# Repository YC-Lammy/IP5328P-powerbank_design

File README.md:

# IP5328P-powerbank_design
 a PD powerbank pcb based on IP5328P chip, feel free to use it
 
 - support QC2.0/QC3.0 output
 - Support FCP input/output
 - Support AFC input/output
 - Support SFCP input/output
 - Support MTK PE1.1&2.0 output
 - Support USB C DRP input/output
 - Support BC1.2, Apple, Samsung
 - Support PD2.0 bi-directional input/output protocol
 - Support PD3.0 input/output and PPS output protocol
 - Support 5V@3.1A, 9V@2.0A, 12V@1.5A voltage output
 
  Kicad nightly 5.99

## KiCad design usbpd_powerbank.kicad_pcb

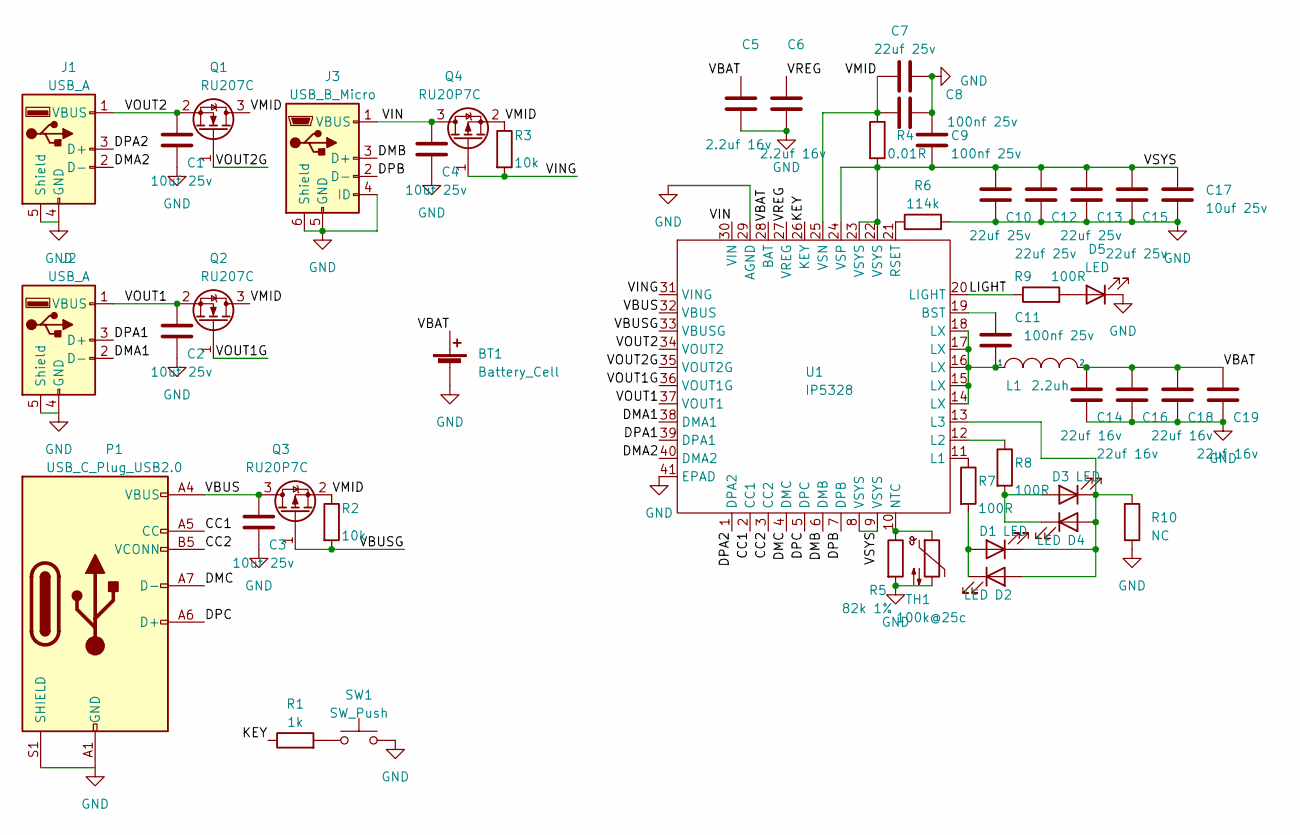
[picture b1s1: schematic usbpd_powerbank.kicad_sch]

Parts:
BT1: Battery_Cell; bat
C1, C2, C3, C4, C17: 10uf 25v; C_0805_2012Metric
C5, C6: 2.2uf 16v; C_0805_2012Metric
C7, C10, C12, C13, C15: 22uf 25v; C_0805_2012Metric
C8, C9, C11: 100nf 25v; C_0603_1608Metric
C14, C16, C18, C19: 22uf 16v; C_0805_2012Metric
D1, D2, D3, D4, D5: LED; LED_0603_1608Metric
J1, J2: USB_A; USB_A_Stewart_SS-52100-001_Horizontal
J3: USB_B_Micro; USB_Micro-B_Amphenol_10103594-0001LF_Horizontal
L1: 2.2uh; L_Wuerth_HCI-1040
P1: USB_C_Plug_USB2.0; USB_C_Receptacle_Palconn_UTC16-G
Q1, Q2: RU207C; SOT-23
Q3, Q4: RU20P7C; SOT-23
R1: 1k; R_0603_1608Metric
R2, R3: 10k; R_0603_1608Metric
R4: 0.01R; R_1206_3216Metric
R5: 82k 1%; R_0603_1608Metric
R6: 114k; R_0603_1608Metric
R7, R8, R9: 100R; R_0603_1608Metric
R10: NC; R_0603_1608Metric
SW1: SW_Push; FPC_2
TH1: 100k@25c; R_0805_2012Metric
U1: IP5328; QFN-40-1EP_6x6mm_P0.5mm_EP4.6x4.6mm

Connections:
/CC1: P1.A5 (CC), U1.2 (CC1)
/CC2: P1.B5 (VCONN), U1.3 (CC2)
/DMA1: J2.2 (D-), U1.38 (DMA1)
/DMA2: J1.2 (D-), U1.40 (DMA2)
/DMB: J3.3 (D+), U1.6 (DMB)
/DMC: P1.A7 (D-), U1.4 (DMC)
/DPA1: J2.3 (D+), U1.39 (DPA1)
/DPA2: J1.3 (D+), U1.1 (DPA2)
/DPB: J3.2 (D-), U1.7 (DPB)
/DPC: P1.A6 (D+), U1.5 (DPC)
/KEY: R1.1, U1.26 (KEY)
/LIGHT: R9.1, U1.20 (LIGHT)
/VBAT: BT1.1 (+), C5.1, C14.1, C16.1, C18.1, C19.1, L1.2, U1.28 (BAT)
/VBUS: C3.1, P1.A4 (VBUS), P1.A9 (VBUS), P1.B4 (VBUS), P1.B9 (VBUS), Q3.3 (D), U1.32 (VBUS)
/VBUSG: Q3.1 (G), R2.2, U1.33 (VBUSG)
/VIN: C4.1, J3.1 (VBUS), Q4.3 (D), U1.30 (VIN)
/VING: Q4.1 (G), R3.2, U1.31 (VING)
/VMID: C7.1, C8.1, Q1.3 (D), Q2.3 (D), Q3.2 (S), Q4.2 (S), R2.1, R3.1, R4.1, U1.25 (VSN)
/VOUT1: C2.1, J2.1 (VBUS), Q2.2 (S), U1.37 (VOUT1)
/VOUT1G: Q2.1 (G), U1.36 (VOUT1G)
/VOUT2: C1.1, J1.1 (VBUS), Q1.2 (S), U1.34 (VOUT2)
/VOUT2G: Q1.1 (G), U1.35 (VOUT2G)
/VREG: C6.1, U1.27 (VREG)
/VSYS: C9.2, C10.1, C12.1, C13.1, C15.1, C17.1, R4.2, U1.8 (VSYS), U1.9 (VSYS), U1.22 (VSYS), U1.23 (VSYS), U1.24 (VSP)
GND: BT1.2 (-), C1.2, C2.2, C3.2, C4.2, C5.2, C6.2, C7.2, C8.2, C9.1, C10.2, C12.2, C13.2, C14.2, C15.2, C16.2, C17.2, C18.2, C19.2, D5.1 (K), J1.4 (GND), J1.5 (Shield), J2.4 (GND), J2.5 (Shield), J3.4 (ID), J3.5 (GND), J3.6 (Shield), P1.A1 (GND), P1.A12 (GND), P1.B1 (GND), P1.B12 (GND), P1.S1 (SHIELD), R5.2, R6.2, R10.2, SW1.2, TH1.2, U1.29 (AGND), U1.41 (EPAD)
unnamed: C11.1, U1.19 (BST)
unnamed: C11.2, L1.1, U1.14 (LX), U1.15 (LX), U1.16 (LX), U1.17 (LX), U1.18 (LX)
unnamed: D1.1 (K), D2.2 (A), D3.1 (K), D4.2 (A), R10.1, U1.13 (L3)
unnamed: D1.2 (A), D2.1 (K), R7.2
unnamed: D3.2 (A), D4.1 (K), R8.2
unnamed: D5.2 (A), R9.2
unnamed: R1.2, SW1.1
unnamed: R5.1, TH1.1, U1.10 (NTC)
unnamed: R6.1, U1.21 (RSET)
unnamed: R7.1, U1.11 (L1)
unnamed: R8.1, U1.12 (L2)

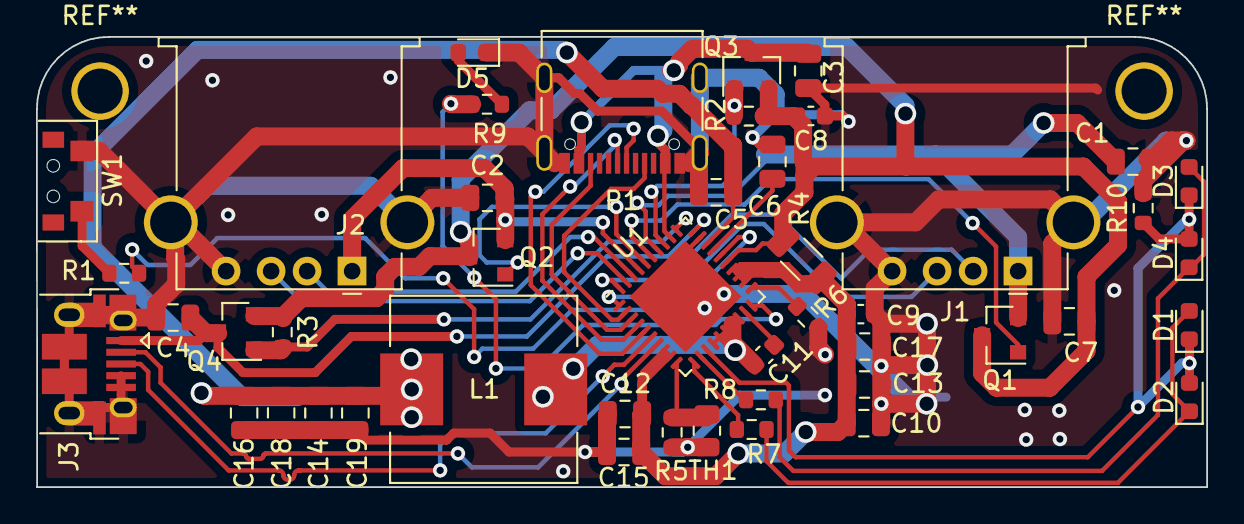
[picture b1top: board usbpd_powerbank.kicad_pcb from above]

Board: 2 copper layers, 65.0 x 25.0 mm, 47 parts (1 on the bottom side), 36 nets.

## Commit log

2021-05-09 upload file
2021-05-09 update photos
